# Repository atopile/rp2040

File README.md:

# RP2040

## Installation
Run in the terminal:

```ato install rp2040```

Add to your ato project:

```import RP2040Kit from "rp2040/rp2040.ato"```

[LINK](https://gitlab.atopile.io/packages/RP2040) to the repo.

## Overview

This package should include all the basics needed to layout an RP2040 microcontroller.

## Features

- **Power Interface:** 3.3v voltage input
- **SPI Interface**
- **I2C Interface** Inter-Integrated Circuit interface for connecting low-speed peripherals.
- **USB 2.0 Interface** Handy to program the rp2040. Hook this up to an usb-c. There is a usb-c in a module as well.
- **GPIO Pins:** General Purpose Input/Output pins for digital input/output functionality.
- **Analog Inputs:** Four analog inputs (A0-A3) for reading analog signals.

## Getting Started

1. **Powering the Module:** Requires a 3.3V supply connected to the power interface.
2. **Connecting Interfaces:** Utilize SPI, I2C, and USB interfaces as per your project requirements.
3. **Utilizing GPIO and Analog Inputs:** Connect your sensors or peripherals to the GPIO or analog inputs as needed.
4. **Programming:** Program the module using your preferred development environment compatible with the RP2040.

## Example Layout

### Layout notes
- Caps should be close to the micro on the 3V3 an 1V1 rails
- 12MHz crystal should be close to micro
- USB series resistors should be close to micro
- Maybe just put everything close to the micro...

## Documentation & Resources

- [Official RP2040 Datasheet](https://datasheets.raspberrypi.com/rp2040/hardware-design-with-rp2040.pdf)

Here is roughly what's going on in the module:

What you have to deal with:

*Courstesy of John Mcmaster*

## Contributing

Contribute to this package using pull requests.

## License

This RP2040 module documentation is provided under the [MIT License](https://opensource.org/license/mit/).

## Contact

For further inquiries or support, please contact us at [narayan@atopile.io](mailto:email@example.com).

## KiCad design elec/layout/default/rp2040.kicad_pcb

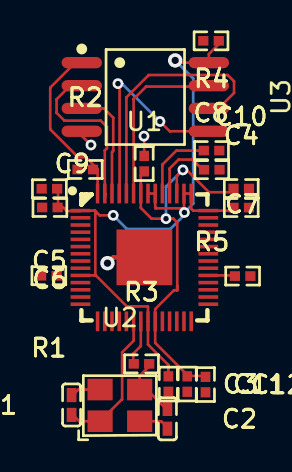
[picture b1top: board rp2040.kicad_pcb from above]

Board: 2 copper layers, 20 parts (0 on the bottom side), 15 nets.

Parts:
C1, C2: 20pF ±5% 50V C0G; C0402-b3ef17
C3, C4, C5, C6, C7, C9, C10, C11: 100nF ±10% 16V X7R; R0402
C8, C12: 1µF ±10% 16V X5R; R0402
R1, R2: 10kΩ ±1% 62.5mW; R0402-56259e
R3: 1kΩ ±1% 62.5mW; R0402-56259e
R4, R5: 27Ω ±1% 62.5mW; R0402-56259e
U1: LQFN-56_L7.0-W7.0-P0.4-EP
U2: OSC-SMD_4P-L3.2-W2.5-BL
U3: SOIC-8_L5.3-W5.3-P1.27-LS8.0-BL

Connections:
cs-1: R2.2, U1.56, U3.1
gnd: C1.2, C2.2, C3.2, C4.2, C5.2, C6.2, C7.2, C8.2, C9.2, C10.2, C11.2, C12.2, U1.19, U1.57, U2.2, U2.4, U3.4
hv: C3.1, C4.1, C5.1, C6.1, C7.1, C8.1, R1.1, R2.1, U1.1, U1.10, U1.22, U1.33, U1.42, U1.43, U1.44, U1.48, U1.49, U3.8
hv-1: C9.1, C10.1, C11.1, C12.1, U1.23, U1.45, U1.50
input: C1.1, U1.20, U2.1
io0: U1.53, U3.5
io1: U1.55, U3.2
io2: U1.54, U3.3
io3: U1.51, U3.7
osc-out: C2.1, R3.2, U2.3
out: R1.2, U1.26
sck: U1.52, U3.6
usb_dm: R5.2, U1.46
usb_dp: R4.1, U1.47
xout: R3.1, U1.21

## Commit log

2023-12-10 Initial commit for RP2040
2023-12-10 Add gitignore
2023-12-10 Init commit, copied RP2040 definition from modules
2023-12-10 Recopied from modules
2023-12-10 Split into two files
2023-12-10 Install footprints here
2023-12-10 Copy Flash IC from modules repo
2023-12-10 Mild tidy of the kit before refactoring with all the new modules
2023-12-10 Add osscilator
2023-12-10 Tidy up osscilator
2023-12-10 Add buildable kit
2023-12-10 Connect iovdd
2023-12-10 remove p in front of oscilator pins
2023-12-10 Add USB-C connector to the kit
2023-12-10 Correct USB interconnect
2023-12-10 remove the ps
2023-12-10 Remove boot pulldown resistor
2023-12-11 Use JLCPCB basic part for flash
2023-12-11 Use 0603 caps by default on the RP2040Kit because they're a basic part at JLCPCB
2023-12-11 fix footprint
2023-12-12 remove usbc from rp2040
2023-12-14 updating footprints to 0402
2023-12-15 Adding readme
2023-12-15 add to readme
2023-12-15 image as well
2023-12-15 fix file name
2023-12-15 update title
2023-12-15 what we deal with
2023-12-16 fix email
2023-12-18 updating to match new generics format
2024-01-01 fix the oscillator res connection
2024-01-06 update the 0.2.0 language spec
2024-01-06 fix value
2024-01-06 update values
2024-01-24 Upgrade for the v0.3.x langauge spec
2024-02-12 update to latest compiler
2024-02-13 added uart interface
2024-02-13 added layout
2024-02-14 added usb interface name with new standard usb2
2024-02-14 fix the layout
2024-02-14 added new spi interface
2024-02-14 swapped button for generic pullup button from generics
2024-02-15 Add interfaces to base RP2040 IC and improve RP2040Kit interfaces
2024-02-17 Refactor power management
    Use inheritance to control power management for the
    RP2040 kit.
    Add an example for 3v3 power from USB using 5v transformer
2024-02-19 one line import and mirror interfaces
2024-02-19 switch to one line import
2024-02-19 mirro interfaces. bump ato version.
2024-02-19 fix usb
2024-02-20 refactor
2024-02-20 refactored kid into core, split USB and 3v3 power into two subclasses
2024-03-01 fixing values for usb resistors
2024-03-01 fixing usb resistors
2024-03-10 fix USB resistors
2024-03-10 Fix ADC power issue
2024-03-19 fixing name conflict for power net
2024-10-28 Remove xmas crud
2025-01-02 Update layout to v0.3 compiler
2025-01-02 Update after fixing net naming collision
2025-01-14 Add new layout properties to PCB
2025-01-16 New properties in layout
2025-04-05 update to kicad 9
2025-04-05 build with latest
